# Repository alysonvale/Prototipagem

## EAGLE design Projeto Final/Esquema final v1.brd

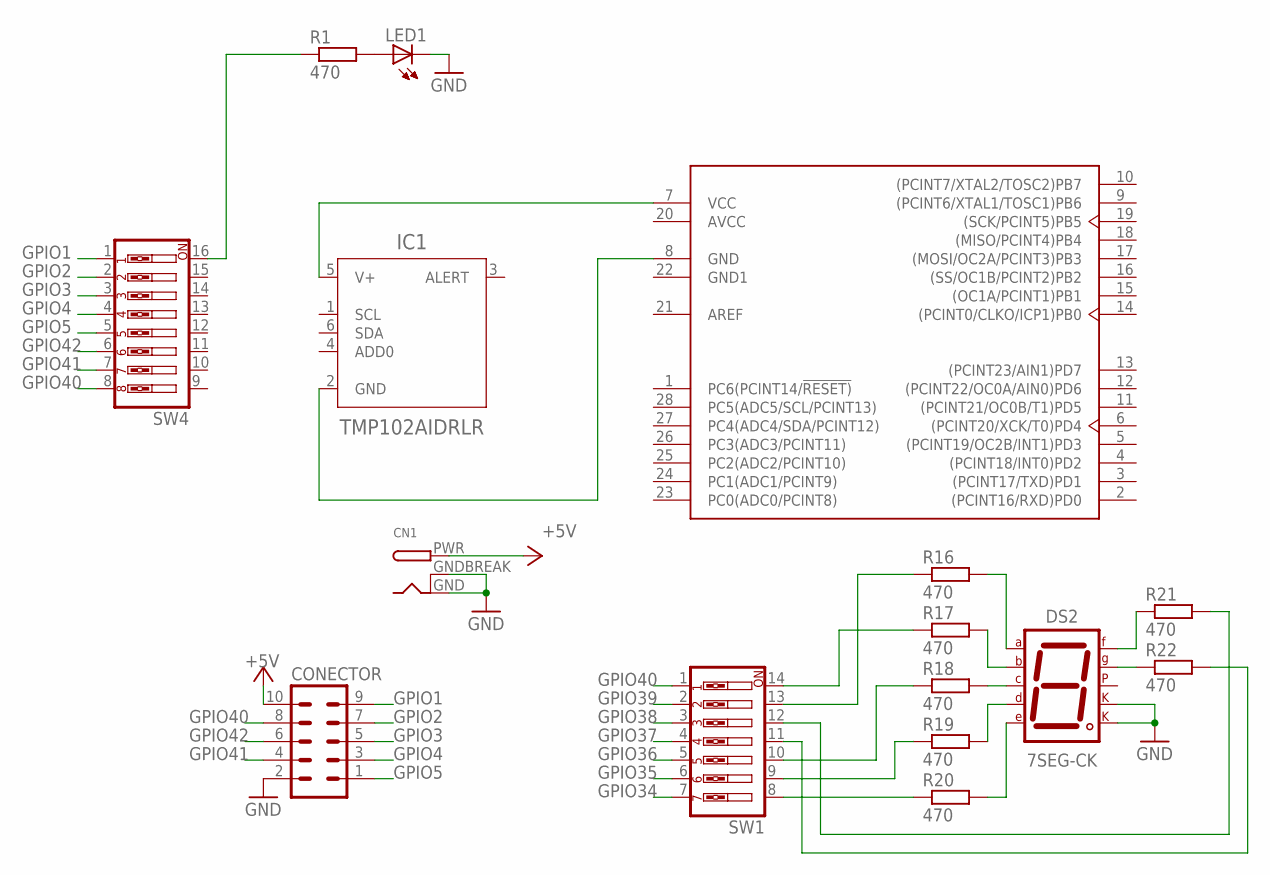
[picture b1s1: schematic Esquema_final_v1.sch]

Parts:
CN1: DCBARRELPTH; DCJACK_2MM_PTH
CONECTOR: MA05-2
DS2: 7SEG-CK; 7SEG-13
IC1: TMP102AIDRLR; SOT563
LED1: LED5MM
R1, R16, R17, R18, R19, R20, R21, R22: 470; 0204V
SW1: SW_DIP-7; EDG-07
SW4: SW_DIP-8; EDG-08
U1: ATMEGA328P-PU; DIP-28

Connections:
+5V: CN1.PWR, CONECTOR.10
AVCC: U1.20 (AVCC)
GND: CN1.GND, CN1.GNDBREAK, CONECTOR.2, DS2.3 (CK1), DS2.8 (CK2), LED1.K (C)
GND1: U1.22 (GND1)
GPIO1: CONECTOR.9, SW4.1
GPIO2: CONECTOR.7, SW4.2
GPIO3: CONECTOR.5, SW4.3
GPIO4: CONECTOR.3, SW4.4
GPIO5: CONECTOR.1, SW4.5
GPIO34: SW1.7
GPIO35: SW1.6
GPIO36: SW1.5
GPIO37: SW1.4
GPIO38: SW1.3
GPIO39: SW1.2
GPIO40: CONECTOR.8, SW1.1, SW4.8
GPIO41: CONECTOR.4, SW4.7
GPIO42: CONECTOR.6, SW4.6
unnamed: IC1.2 (GND), U1.8 (GND)
unnamed: LED1.A, R1.2
unnamed: IC1.5 (V+), U1.7 (VCC)
unnamed: DS2.10 (G), R22.1
unnamed: DS2.9 (F), R21.1
unnamed: DS2.4 (C), R18.2
unnamed: DS2.2 (D), R19.2
unnamed: R1.1, SW4.16
unnamed: DS2.1 (E), R20.2
unnamed: DS2.6 (B), R17.2
unnamed: DS2.7 (A), R16.2
unnamed: R19.1, SW1.9
unnamed: R18.1, SW1.10
unnamed: R17.1, SW1.14
unnamed: R16.1, SW1.13
unnamed: R21.2, SW1.12
unnamed: R22.2, SW1.11
unnamed: R20.1, SW1.8

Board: 2 copper layers, 16 parts (0 on the bottom side), 28 nets, no tracks yet.
